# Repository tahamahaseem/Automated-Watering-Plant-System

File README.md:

# Automated-Watering-Plant-System

Arduino-based water plant system automates indoor plant care. Monitors temperature, humidity, watering, and light for optimal growth. User-friendly programming with Arduino Uno R3. Affordable and practical solution for hassle-free plant maintenance. 

## Repository Structure

The repository is structured as follows:

- `ProjectCode.ino`: This is the main Arduino sketch file that contains the final code for the water plant system. It integrates all the sub-portions of the system.
- `.brd`: Schematic capture and PCB
- `.sch`: Circuit schematic file

Other folders include:

- `Humidity_Sensor`: This folder contains the code for the humidity sensor. It has its own `Humidity_Sensor.ino` file that controls the functionality of the humidity sensor.
- `Moisture_Sensor`: This folder contains the code for the moisture sensor. It has its own `Moisture_Sensor.ino` file that controls the functionality of the moisture sensor.
- `RTC`: This folder contains the code for the Real-Time Clock (RTC) module. It has its own `RTC.ino` file that controls the functionality of the RTC.
- `Bluetooth`: This folder contains the code for the Bluetooth module. It has its own `Bluetooth.ino` file that controls the functionality of the Bluetooth module.
- `ds3231_RTC`: This folder contains the code for the DS3231 RTC module. It has its own `ds3231_RTC.ino` file that controls the functionality of the DS3231 RTC module.

## Arduino Setup

Follow these steps to set up the system:

1. Connect the Arduino board to your computer.
2. Open the `ProjectCode.ino` file in the Arduino IDE.
3. Upload the code to the Arduino board.
4. Connect all sensors and actuators to the correct pins using the schematics provided on the Arduino board. 
5. Make sure all the required libraries provided are installed for the respective sensors, actuators, and modules. 
6. Power on the Arduino board.
7. The system is now ready to use.

All resources needed are provided here: https://github.com/tahamahaseem/Automated-Watering-Plant-System/blob/main/README.md#resources

## System Overview

The Water Plant System consists of several sensors and actuators that work together to ensure optimal plant care. The system includes the following components:

- LCD Display: Shows data from different sensors.
- Sensors:
  - Photoresistor: Measures light levels.
  - Pushbutton: Switches between different data displayed on the LCD.
  - Water level sensor: Detects the water level in the tank.
  - Temperature and humidity sensor: Measures the ambient temperature and humidity.
  - Capacitive soil moisture sensor: Measures soil moisture levels.
  - DS3231 RTC Module: Provides real-time clock functionality.
- Actuators:
  - Water DC pump: Supplies water to the plants.
  - Buzzer: Produces audible alerts.
  - DC fan: Controls air circulation and humidity.
  - Servo motor vent: Controls ventilation.
  - 8x8 LED matrix: Provides plant growth lighting.

## System Usage

1. Power on the Water Plant System by connecting it to a power source.

2. The LCD Display will show the current data page

3. To switch between different data pages on the LCD Display, press and release the pushbutton. Each press will cycle to the next data page.

4. The available data pages on the LCD Display are:
   - Temperature and humidity levels
   - Water levels in the tank
   - Light levels
   - Soil moisture levels
   - Time since the plants were last watered

5. To obtain accurate readings, ensure that all sensors are properly connected and positioned.

6. The water pump operates based on the water level and soil moisture readings:
   - If the water levels in the tank are low or empty, the water pump will be temporarily turned off until the tank is filled to a reasonable range.
   - If the soil moisture levels are below 20%, indicating dry soil, the water pump will be activated to water the plants. This only occurs if there is water in the tank.

7. The system relies on the DS3231 RTC Module for timing and control. The RTC is used as a cooldown mechanism for the water pump. After each pump activation (1500 milliseconds), the RTC time is reset and waits for a minute to elapse before the pump can be activated again if necessary. This ensures controlled watering intervals.

8. The DC fan and servo motor vent help maintain appropriate humidity and temperature levels in the plant's environment. When the humidity levels go above 50% or the temperature exceeds 28 degrees Celsius, both the fan and the vent will activate to reduce moisture and increase airflow.

9. The photoresistor and the 8x8 LED matrix control the plant growth lighting. When the photoresistor senses darkness, the LED matrix will turn on to provide blue and red lights, which are optimal for plant growth. When sufficient or extreme light is detected, the LED matrix will turn off.

## Maintenance

- Ensure that the water tank is regularly filled to an appropriate level to ensure uninterrupted watering.

- Check the soil moisture sensor readings periodically and adjust the watering thresholds if necessary.

- Monitor the functionality of the water pump, fan, and servo motor. If any issues arise, check the connections and troubleshoot accordingly.

- Keep an eye on the water level sensor readings to ensure its accuracy. If inconsistent readings occur, consider replacing the sensor.

- Verify the functionality of the humidity and temperature sensor to ensure accurate environmental control. If unusual readings are observed, check the sensor and replace it if necessary.

## Troubleshooting
If you encounter any issues with the Water Plant System, consider the following troubleshooting steps:

1. Check the power supply and connections to ensure everything is properly connected.

2. Verify that all sensors and actuators are correctly connected and positioned.

3. Ensure that the code is correctly uploaded to the microcontroller and check for any error messages.

4. Inspect the system components for any visible damage or loose connections.

## Resources 

### Sensors and Actuators

To use this water plant system, you will need the following components:

- 1 12V Water Pump	
- 1 LED Matrix	
- 1 DC Fan	
- 1 HC-06 Bluetooth	 	
- 1 LCD screen
- 1 PCF8574t	
- 3 Resistors (1K)	 
- 1 Push button	 
- 2 DC relay	 
- 1 Photoresistor	 
- 1 DHT (temperature and humidity sensor)	 
- 1 Water Level Sensor	
- 1 Capacitive Soil Moisture Sensor	
- F-F jumper cable packs	
- 1 tubing
- 1 DS3231 RTC I2C 

### Libraries

- `RTClib.h`: Used for RTC module
- `LiquidCrystal_I2C.h`: Used for	LCD and I2C Communication
- `dht.h`: Used for	Humidity and Temperature Sensor
- `FastLED.h`: Used for	8X8 LED Matrix
- `Servo.h`: Used for	Servo Motor

### Design

#### Arduino Pin Layout

#### PCB Design

#### Algorithm

#### Servo Vent 3D Model

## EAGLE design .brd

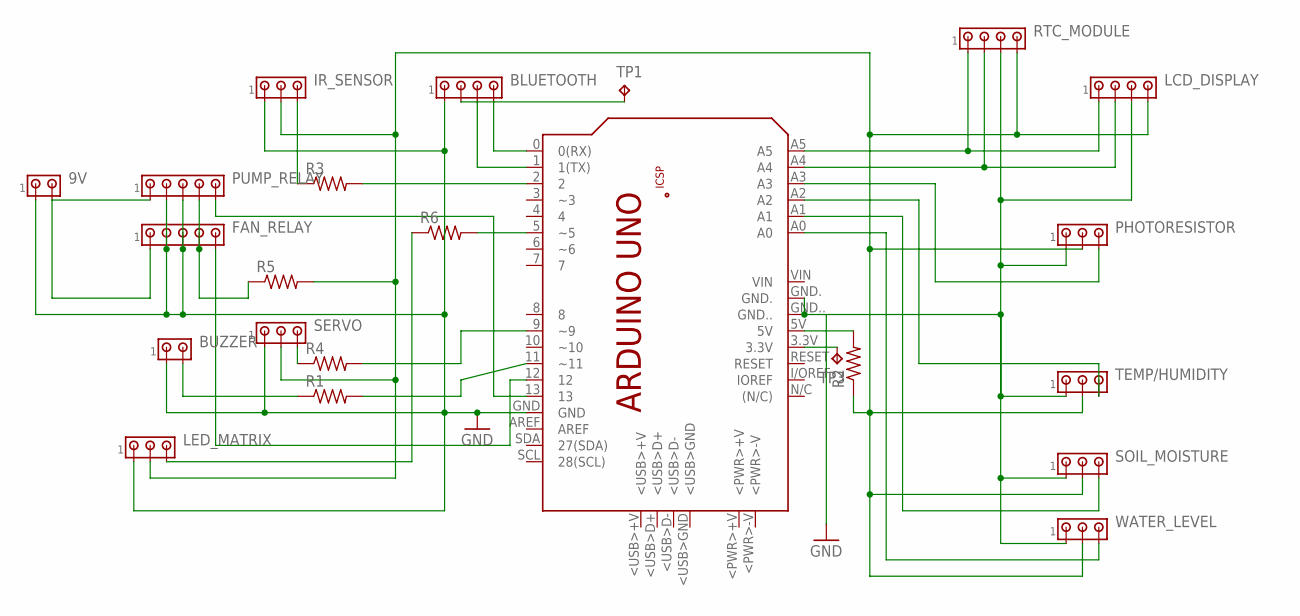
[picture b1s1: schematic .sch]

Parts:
9V: MTA02-100; 10X02MTA
BLUETOOTH: MTA04-100; 10X04MTA
BUZZER: MTA02-100; 10X02MTA
FAN_RELAY: MTA05-100; 10X05MTA
IR_SENSOR: MTA03-100; 10X03MTA
LCD_DISPLAY: MTA04-100; 10X04MTA
LED_MATRIX: MTA03-100; 10X03MTA
PCB1: ARDUINO_UNO
PHOTORESISTOR: MTA03-100; 10X03MTA
PUMP_RELAY: MTA05-100; 10X05MTA
R1, R2, R3, R4, R5, R6: R-US_0204/7; 0204/7
RTC_MODULE: MTA04-100; 10X04MTA
SERVO: MTA03-100; 10X03MTA
SOIL_MOISTURE: MTA03-100; 10X03MTA
TEMP/HUMIDITY: MTA03-100; 10X03MTA
TP1, TP3: TPPAD1-17Y; P1-17Y
WATER_LEVEL: MTA03-100; 10X03MTA

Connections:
GND: 9V.1, BLUETOOTH.1, BUZZER.1, FAN_RELAY.2, FAN_RELAY.3, IR_SENSOR.1, LCD_DISPLAY.3, LED_MATRIX.1, PCB1.GND, PCB1.GND., PCB1.GND.., PHOTORESISTOR.1, PUMP_RELAY.2, PUMP_RELAY.3, RTC_MODULE.3, SERVO.1, SOIL_MOISTURE.1, TEMP/HUMIDITY.1, WATER_LEVEL.1
unnamed: BLUETOOTH.4, PCB1.0 (0(RX))
unnamed: BLUETOOTH.3, PCB1.1 (1(TX))
unnamed: BLUETOOTH.2, TP1.TP
unnamed: 9V.2, FAN_RELAY.1, PUMP_RELAY.1
unnamed: IR_SENSOR.2, LCD_DISPLAY.4, LED_MATRIX.2, PHOTORESISTOR.2, R2.1, R5.2, RTC_MODULE.4, SERVO.2, SOIL_MOISTURE.2, TEMP/HUMIDITY.2, WATER_LEVEL.2
unnamed: PCB1.9 (~9), R4.2
unnamed: FAN_RELAY.5, PCB1.12
unnamed: PCB1.13, PUMP_RELAY.5
unnamed: IR_SENSOR.3, R3.1
unnamed: LCD_DISPLAY.1, PCB1.A5, RTC_MODULE.1
unnamed: LCD_DISPLAY.2, PCB1.A4, RTC_MODULE.2
unnamed: PCB1.A2, TEMP/HUMIDITY.3
unnamed: PCB1.A3, PHOTORESISTOR.3
unnamed: PCB1.A1, SOIL_MOISTURE.3
unnamed: PCB1.A0, WATER_LEVEL.3
unnamed: BUZZER.2, R1.1
unnamed: PCB1.11 (~11), R1.2
unnamed: PCB1.3.3V, TP3.TP
unnamed: PCB1.5V, R2.2
unnamed: PCB1.2, R3.2
unnamed: R4.1, SERVO.3
unnamed: FAN_RELAY.4, PUMP_RELAY.4, R5.1
unnamed: LED_MATRIX.3, R6.1
unnamed: PCB1.5 (~5), R6.2

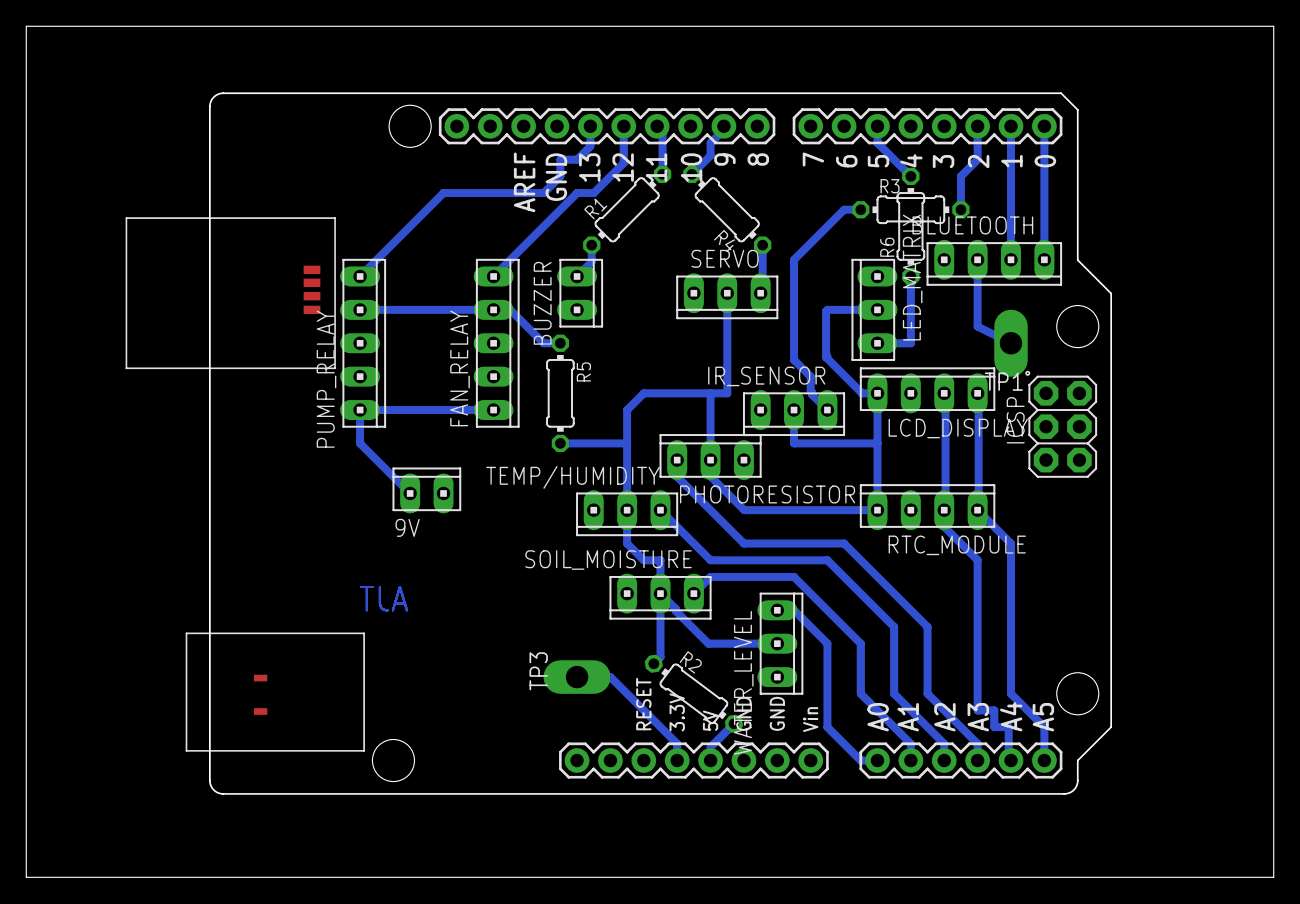
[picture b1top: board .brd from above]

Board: 2 copper layers, 94.8 x 64.6 mm, 23 parts (0 on the bottom side), 25 nets.
